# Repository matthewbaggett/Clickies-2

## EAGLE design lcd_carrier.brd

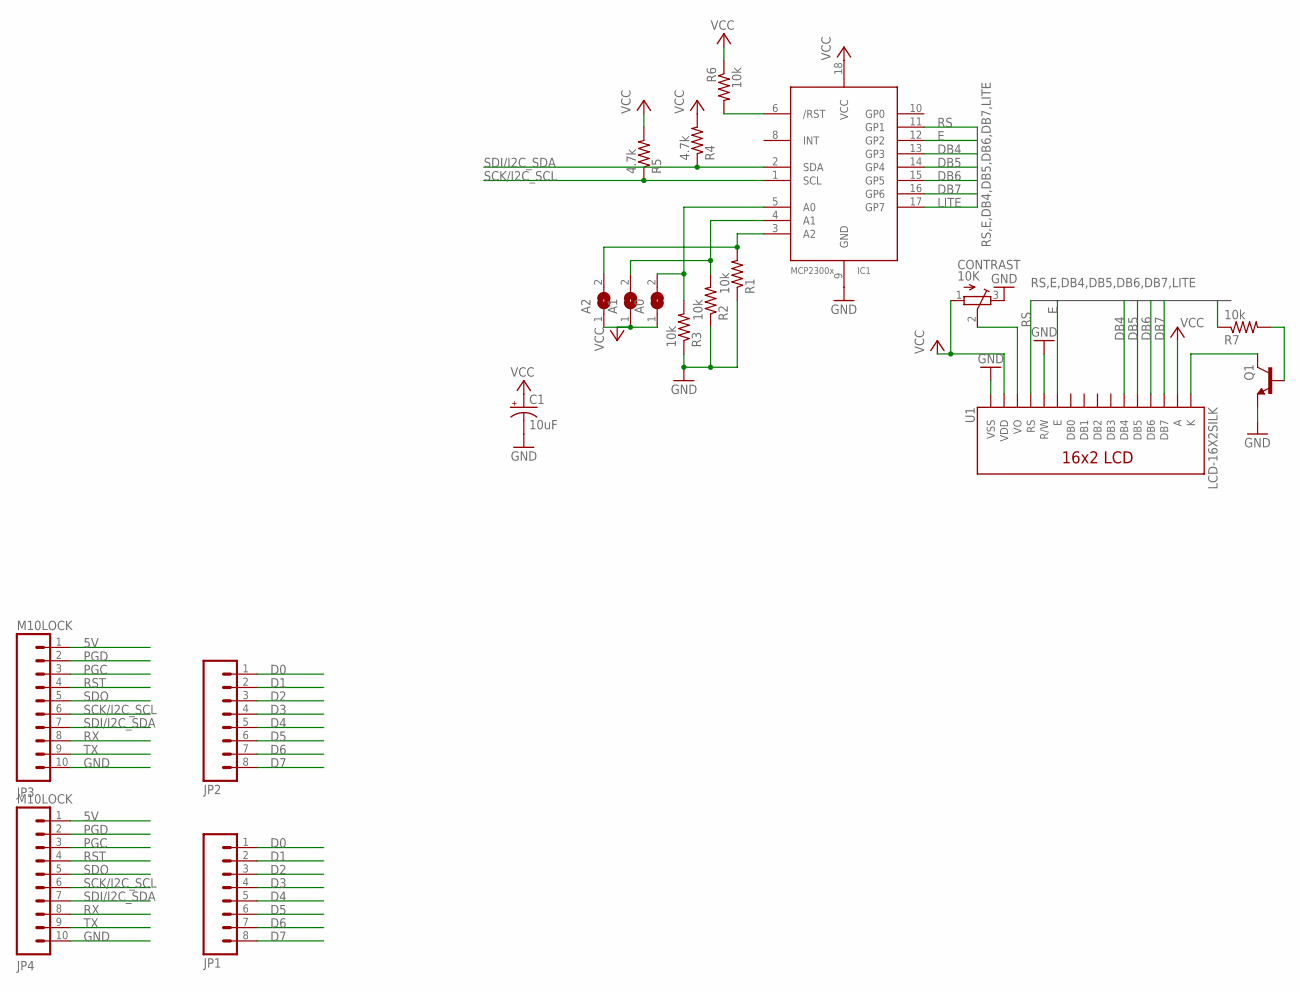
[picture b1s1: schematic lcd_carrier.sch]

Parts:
A0, A1, A2: SJ
C1: 10uF; A/3216-18R
CONTRAST: 10K; TC33X
IC1: MCP2300X/SO; SO18W
JP1, JP2: M08LOCK; 1X08_LOCK
JP3, JP4: M10LOCK; 1X10_LOCK
Q1: MMBT2222ALT1-NPN-SOT23-BEC; SOT23-BEC
R1, R2, R3, R6, R7: 10k; R0805
R4, R5: 4.7k; R0805
U1: LCD-16X2SILK; LCD-16X2

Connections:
5V: JP3.1, JP4.1
D0: JP1.1, JP2.1
D1: JP1.2, JP2.2
D2: JP1.3, JP2.3
D3: JP1.4, JP2.4
D4: JP1.5, JP2.5
D5: JP1.6, JP2.6
D6: JP1.7, JP2.7
D7: JP1.8, JP2.8
DB4: IC1.13 (GP3), U1.11 (DB4)
DB5: IC1.14 (GP4), U1.12 (DB5)
DB6: IC1.15 (GP5), U1.13 (DB6)
DB7: IC1.16 (GP6), U1.14 (DB7)
E: IC1.12 (GP2), U1.6 (E)
GND: C1.-, CONTRAST.3 (E), IC1.9 (GND), JP3.10, JP4.10, Q1.E, R1.1, R2.1, R3.1, U1.1 (VSS), U1.5 (R/W)
LITE: IC1.17 (GP7), R7.1
unnamed: A0.2, IC1.5 (A0), R3.2
unnamed: IC1.6 (/RST), R6.2
unnamed: A1.2, IC1.4 (A1), R2.2
unnamed: A2.2, IC1.3 (A2), R1.2
unnamed: Q1.C, U1.16 (K)
unnamed: Q1.B, R7.2
unnamed: CONTRAST.2 (S), U1.3 (VO)
PGC: JP3.3, JP4.3
PGD: JP3.2, JP4.2
RS: IC1.11 (GP1), U1.4 (RS)
RST: JP3.4, JP4.4
RX: JP3.8, JP4.8
SCK/I2C_SCL: IC1.1 (SCL), JP3.6, JP4.6, R5.1
SDI/I2C_SDA: IC1.2 (SDA), JP3.7, JP4.7, R4.1
SDO: JP3.5, JP4.5
TX: JP3.9, JP4.9
VCC: A0.1, A1.1, A2.1, C1.+, CONTRAST.1 (A), IC1.18 (VCC), R4.2, R5.2, R6.1, U1.2 (VDD), U1.15 (A)

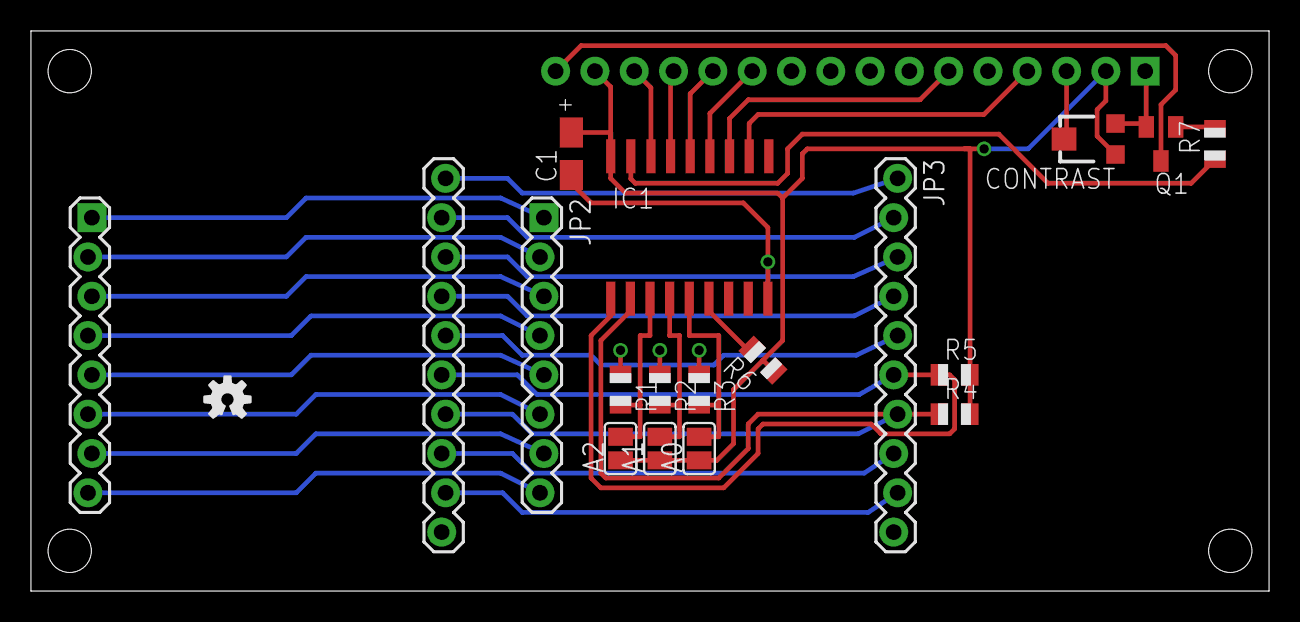
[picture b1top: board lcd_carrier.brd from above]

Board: 2 copper layers, 80.0 x 36.2 mm, 20 parts (1 on the bottom side), 33 nets.

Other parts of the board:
U$1: OSHW-LOGO-S

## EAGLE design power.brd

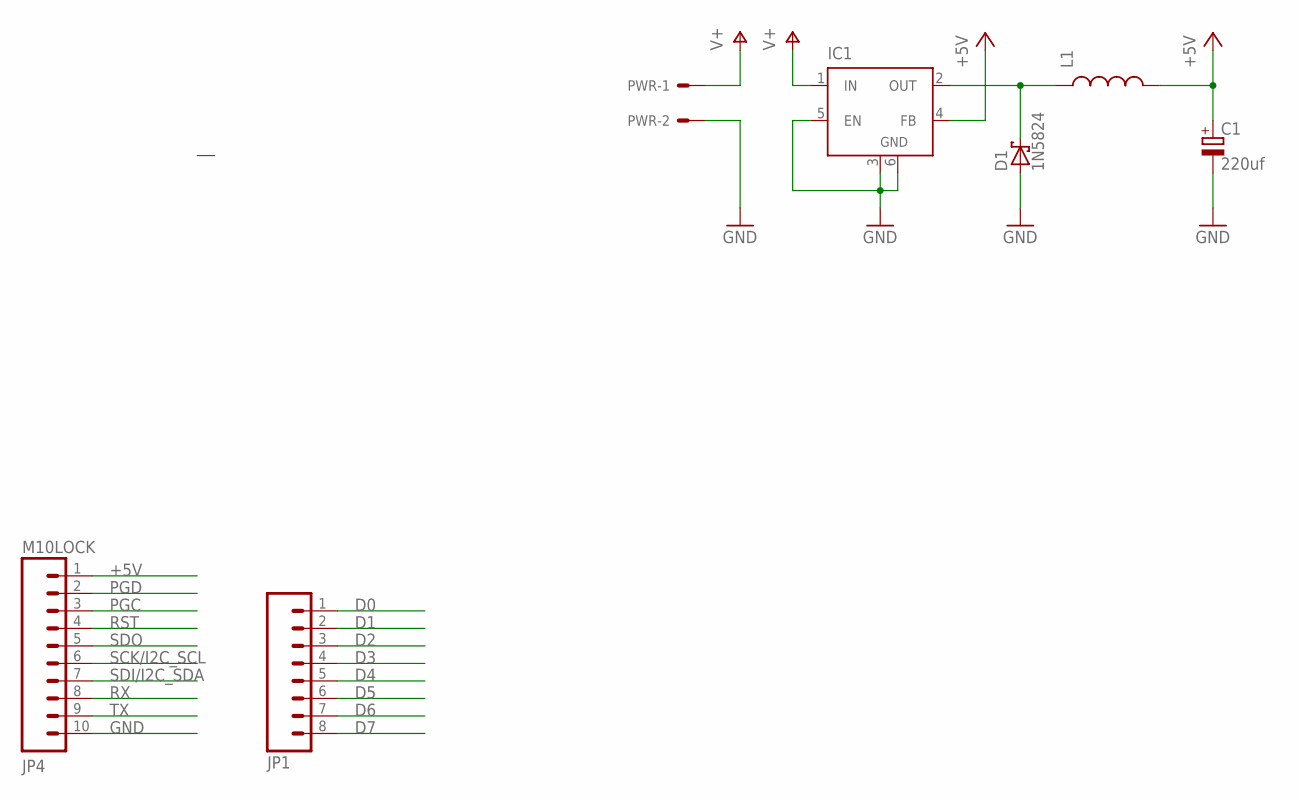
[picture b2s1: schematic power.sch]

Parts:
C1: 220uf; E2,5-6
D1: 1N5824; DO41-7.6
IC1: LM2596S; TO263-5
JP1: M08LOCK; 1X08_LOCK
JP4: M10LOCK; 1X10_LOCK
L1: INDUCTORSRU1038; SRU1038
PWR: 22-05-7028-02; 7395-02

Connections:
+5V: C1.+, IC1.4 (FB), JP4.1, L1.2
D0: JP1.1
D1: JP1.2
D2: JP1.3
D3: JP1.4
D4: JP1.5
D5: JP1.6
D6: JP1.7
D7: JP1.8
GND: C1.-, D1.A, IC1.3 (GND), IC1.5 (EN), IC1.6 (GND), JP4.10, PWR.2
PGC: JP4.3
PGD: JP4.2
RST: JP4.4
RX: JP4.8
SCK/I2C_SCL: JP4.6
SDI/I2C_SDA: JP4.7
SDO: JP4.5
TX: JP4.9
V+: IC1.1 (IN), PWR.1
VOUT: D1.C, IC1.2 (OUT), L1.1

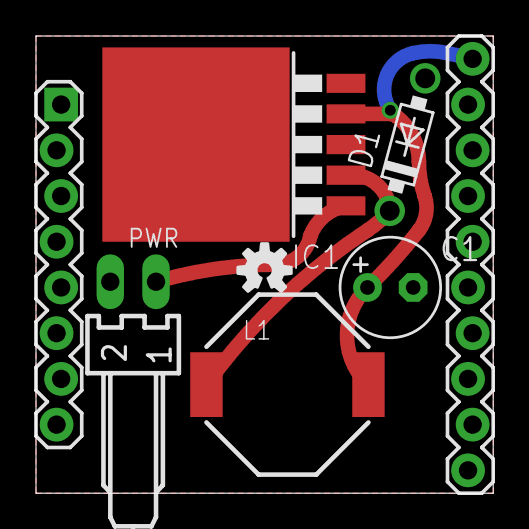
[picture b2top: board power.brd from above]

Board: 2 copper layers, 25.4 x 25.4 mm, 8 parts (0 on the bottom side), 4 nets.

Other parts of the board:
U$1: OSHW-LOGO-S

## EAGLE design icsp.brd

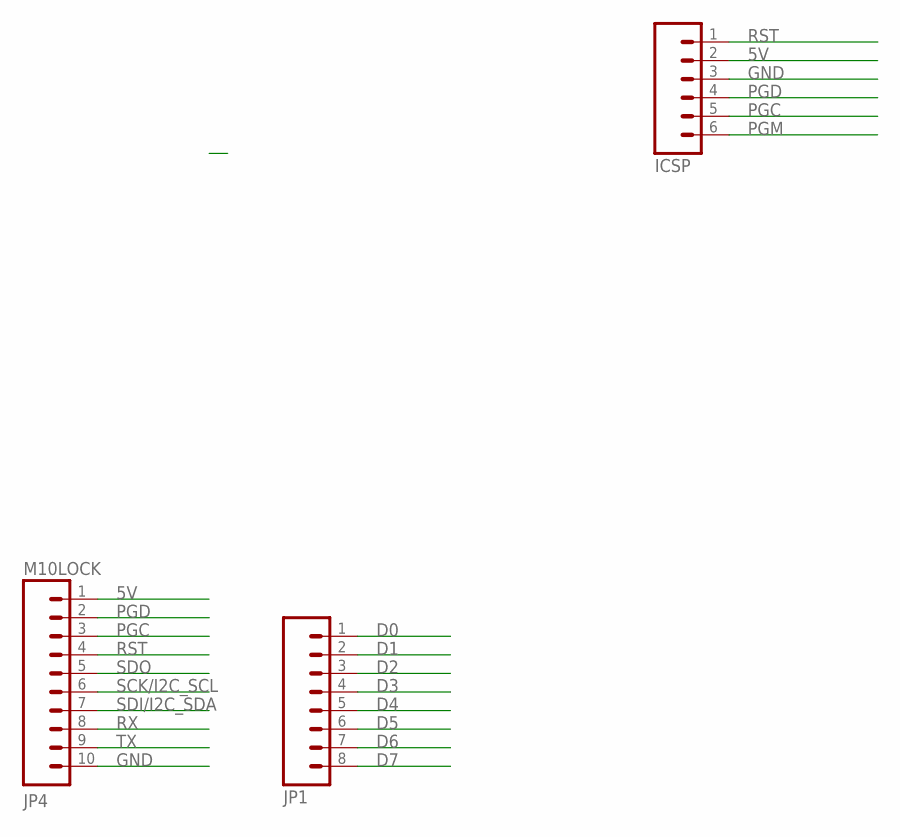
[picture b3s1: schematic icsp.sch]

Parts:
ICSP: M06LOCK; 1X06_LOCK
JP1: M08LOCK; 1X08_LOCK
JP4: M10LOCK; 1X10_LOCK

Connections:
5V: ICSP.2, JP4.1
D0: JP1.1
D1: JP1.2
D2: JP1.3
D3: JP1.4
D4: JP1.5
D5: JP1.6
D6: JP1.7
D7: JP1.8
GND: ICSP.3, JP4.10
PGC: ICSP.5, JP4.3
PGD: ICSP.4, JP4.2
PGM: ICSP.6
RST: ICSP.1, JP4.4
RX: JP4.8
SCK/I2C_SCL: JP4.6
SDI/I2C_SDA: JP4.7
SDO: JP4.5
TX: JP4.9

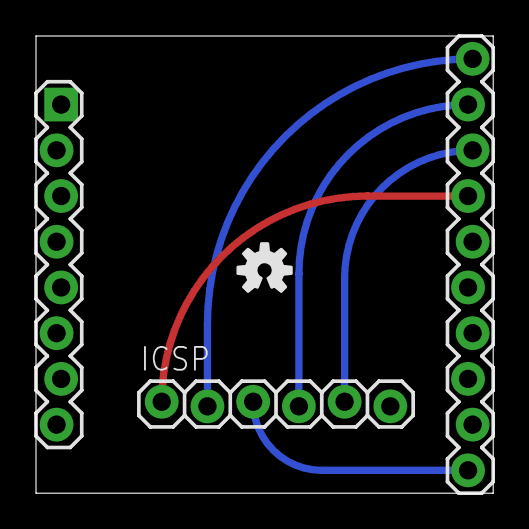
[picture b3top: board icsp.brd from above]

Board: 2 copper layers, 25.4 x 25.4 mm, 4 parts (0 on the bottom side), 5 nets.

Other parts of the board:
U$1: OSHW-LOGO-S

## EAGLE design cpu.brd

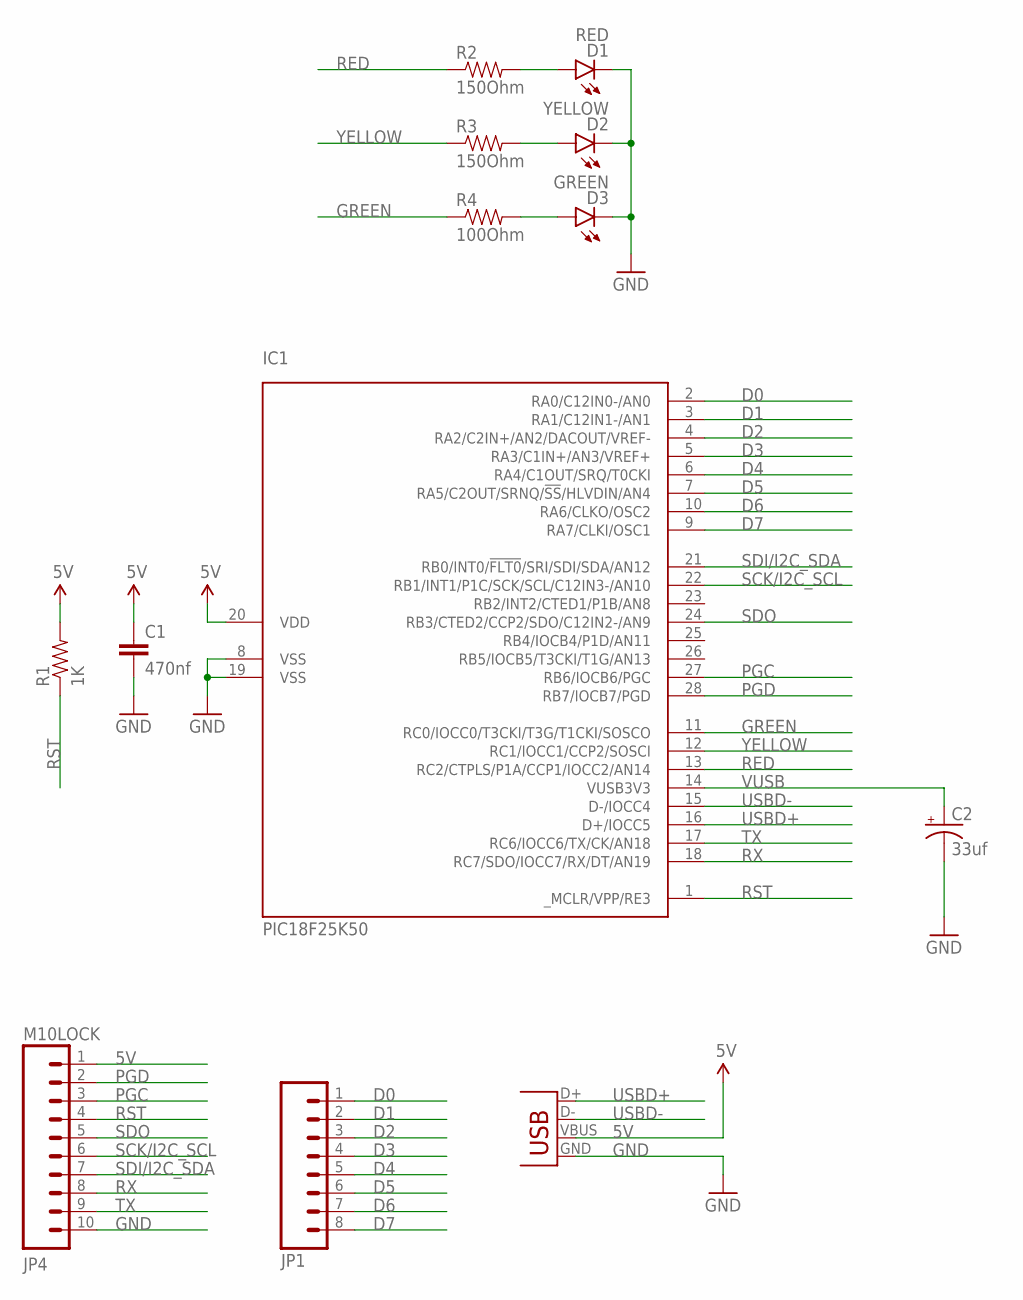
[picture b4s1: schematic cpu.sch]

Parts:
C1: 470nf; 0805
C2: 33uf; PANASONIC_D
D1: RED; LED-0603
D2: YELLOW; LED-0603
D3: GREEN; LED-0603
IC1: PIC18F25K50; SO-28W
JP1: M08LOCK; 1X08_LOCK
JP3: USBSMD; USB-MINIB
JP4: M10LOCK; 1X10_LOCK
R1: 1K; 0603-RES
R2, R3: 150Ohm; 0402-RES
R4: 100Ohm; 0402-RES

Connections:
5V: C1.1, IC1.20 (VDD), JP3.VBUS, JP4.1, R1.2
D0: IC1.2 (RA0/C12IN0-/AN0), JP1.1
D1: IC1.3 (RA1/C12IN1-/AN1), JP1.2
D2: IC1.4 (RA2/C2IN+/AN2/DACOUT/VREF-), JP1.3
D3: IC1.5 (RA3/C1IN+/AN3/VREF+), JP1.4
D4: IC1.6 (RA4/C1OUT/SRQ/T0CKI), JP1.5
D5: IC1.7 (RA5/C2OUT/SRNQ/!SS!/HLVDIN/AN4), JP1.6
D6: IC1.10 (RA6/CLKO/OSC2), JP1.7
D7: IC1.9 (RA7/CLKI/OSC1), JP1.8
GND: C1.2, C2.-, D1.C, D2.C, D3.C, IC1.8 (VSS), IC1.19 (VSS), JP3.GND, JP4.10
GREEN: IC1.11 (RC0/IOCC0/T3CKI/T3G/T1CKI/SOSCO), R4.1
unnamed: D1.A, R2.2
unnamed: D2.A, R3.2
unnamed: D3.A, R4.2
PGC: IC1.27 (RB6/IOCB6/PGC), JP4.3
PGD: IC1.28 (RB7/IOCB7/PGD), JP4.2
RED: IC1.13 (RC2/CTPLS/P1A/CCP1/IOCC2/AN14), R2.1
RST: IC1.1 (_MCLR/VPP/RE3), JP4.4, R1.1
RX: IC1.18 (RC7/SDO/IOCC7/RX/DT/AN19), JP4.8
SCK/I2C_SCL: IC1.22 (RB1/INT1/P1C/SCK/SCL/C12IN3-/AN10), JP4.6
SDI/I2C_SDA: IC1.21 (RB0/INT0/!FLT0!/SRI/SDI/SDA/AN12), JP4.7
SDO: IC1.24 (RB3/CTED2/CCP2/SDO/C12IN2-/AN9), JP4.5
TX: IC1.17 (RC6/IOCC6/TX/CK/AN18), JP4.9
USBD+: IC1.16 (D+/IOCC5), JP3.D+
USBD-: IC1.15 (D-/IOCC4), JP3.D-
VUSB: C2.+, IC1.14 (VUSB3V3)
YELLOW: IC1.12 (RC1/IOCC1/CCP2/SOSCI), R3.1

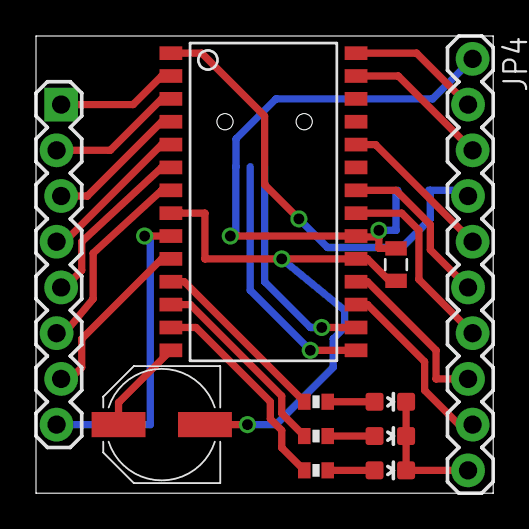
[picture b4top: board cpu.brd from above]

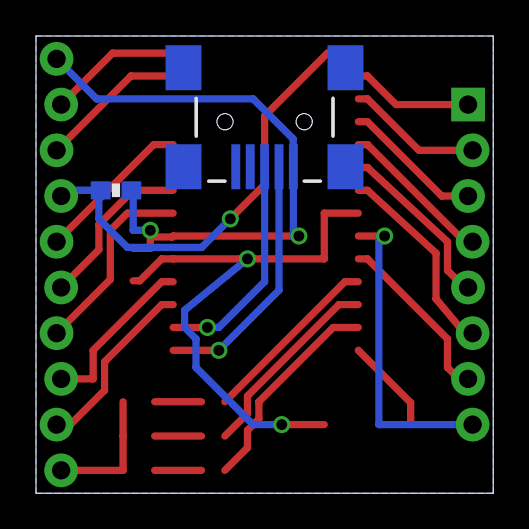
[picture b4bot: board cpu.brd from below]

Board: 2 copper layers, 25.4 x 25.4 mm, 13 parts (2 on the bottom side), 27 nets.

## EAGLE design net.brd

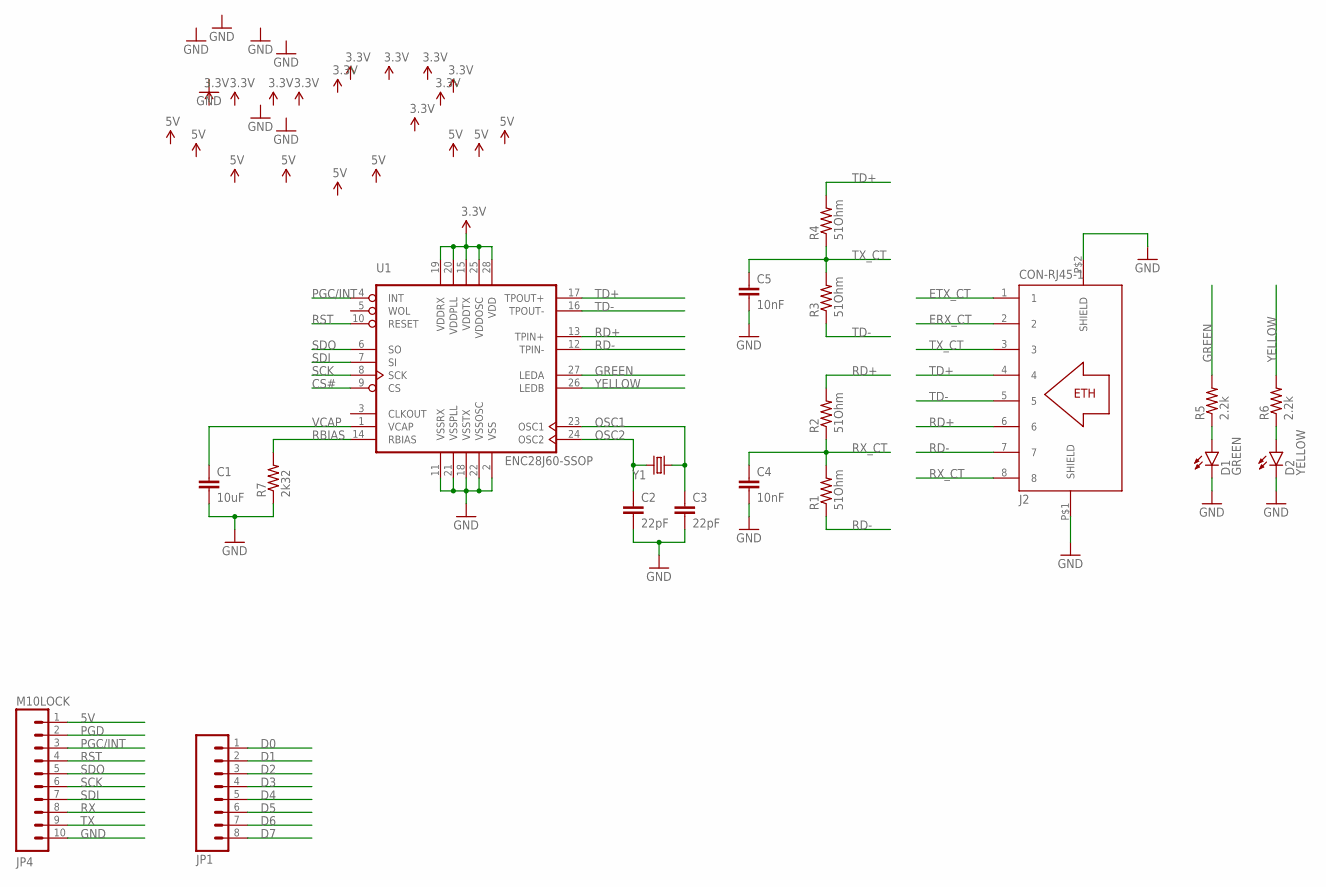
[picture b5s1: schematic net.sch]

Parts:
C1: 10uF; 0603-CAP
C2, C3: 22pF; 0603-CAP
C4, C5: 10nF; 0603-CAP
D1: GREEN; LED-0603
D2: YELLOW; LED-0603
J2: CON-RJ45-1; GM-SMT2-S2-88
JP1: M08LOCK; 1X08_LOCK
JP4: M10LOCK; 1X10_LOCK
R1, R2, R3, R4: 51Ohm; 0603
R5, R6: 2.2k; 0603-RES
R7: 2k32; 0603-RES
U1: ENC28J60-SSOP; SSOP28
Y1: CRYSTAL5X3; CRYSTAL-SMD-5X3

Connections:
3.3V: U1.15 (VDDTX), U1.19 (VDDRX), U1.20 (VDDPLL), U1.25 (VDDOSC), U1.28 (VDD)
5V: JP4.1
CS#: U1.9 (CS)
D0: JP1.1
D1: JP1.2
D2: JP1.3
D3: JP1.4
D4: JP1.5
D5: JP1.6
D6: JP1.7
D7: JP1.8
ERX_CT: J2.2
ETX_CT: J2.1
GND: C1.2, C2.2, C3.2, C4.2, C5.2, D1.C, D2.C, J2.P$1 (SHIELD), J2.P$2 (SHIELD), JP4.10, R7.1, U1.2 (VSS), U1.11 (VSSRX), U1.18 (VSSTX), U1.21 (VSSPLL), U1.22 (VSSOSC)
GREEN: R5.2, U1.27 (LEDA)
unnamed: D1.A, R5.1
unnamed: D2.A, R6.1
OSC1: C3.1, U1.23 (OSC1), Y1.1
OSC2: C2.1, U1.24 (OSC2), Y1.3 (2)
PGC/INT: JP4.3, U1.4 (INT)
PGD: JP4.2
RBIAS: R7.2, U1.14 (RBIAS)
RD+: J2.6, R2.2, U1.13 (TPIN+)
RD-: J2.7, R1.1, U1.12 (TPIN-)
RST: JP4.4, U1.10 (RESET)
RX: JP4.8
RX_CT: C4.1, J2.8, R1.2, R2.1
SCK: JP4.6, U1.8 (SCK)
SDI: JP4.7, U1.7 (SI)
SDO: JP4.5, U1.6 (SO)
TD+: J2.4, R4.2, U1.17 (TPOUT+)
TD-: J2.5, R3.1, U1.16 (TPOUT-)
TX: JP4.9
TX_CT: C5.1, J2.3, R3.2, R4.1
VCAP: C1.1, U1.1 (VCAP)
YELLOW: R6.2, U1.26 (LEDB)

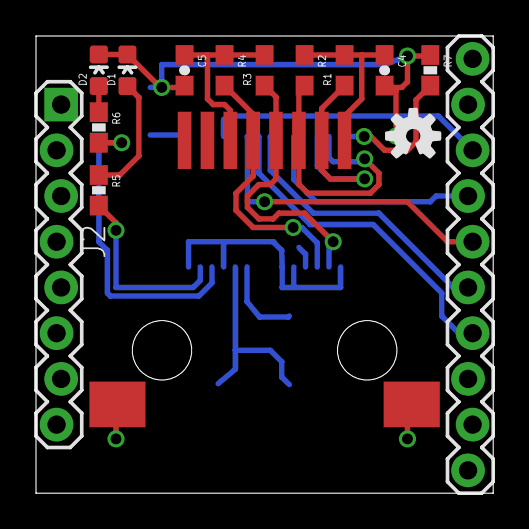
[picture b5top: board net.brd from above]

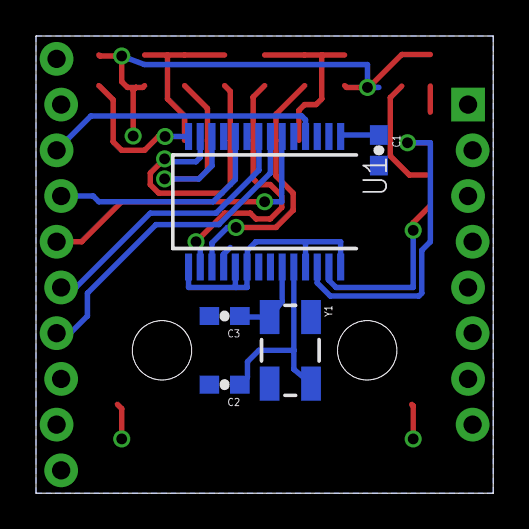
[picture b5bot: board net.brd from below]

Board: 2 copper layers, 25.4 x 25.4 mm, 20 parts (5 on the bottom side), 21 nets.

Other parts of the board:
U$1: OSHW-LOGO-S

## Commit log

2014-10-16 Initial commit after redoing clickies from scratch to use a PIC18F25K50 instead of 14K20
2014-10-16 add lcd carrier
2014-10-16 Adding LCD carrier board
2014-11-28 Changes I forgot to commit
2015-12-29 Do not commit the eagle.epf file
2015-12-29 add eagle.epf to ignore
2016-06-13 Fix typos

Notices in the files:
parts and their libraries:
SparkFun-Connectors: Licensing: Creative Commons ShareAlike 4.0 International - https://creativecommons.org/licenses/by-sa/4.0
m-pad-2.1: License : GNU General Public License version 2 (see bottom)
